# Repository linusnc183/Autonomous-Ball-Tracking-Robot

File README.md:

# Autonomous Ball Tracking Robot

A two-wheeled robot that visually tracks and follows a red ball. A Raspberry Pi handles vision (Picamera2 + OpenCV) and sends drive commands over UART to a custom STM32-based motor controller PCB, which closes the loop with encoder feedback and PID.

I designed the controller PCB from scratch in KiCad and wrote the embedded firmware in C (STM32CubeIDE, HAL).

**Skills demonstrated:** PCB design (KiCad) · embedded C / STM32 HAL · real-time control loops (PID) · analog/digital circuit design (power regulation, signal protection) · computer vision (OpenCV) · serial communication protocol design

https://github.com/user-attachments/assets/ed4e9871-f768-4ec5-b8f6-aebbd3194bc8

## Table of Contents

- [Features](#features)
- [System Architecture](#system-architecture)
- [Hardware](#hardware)
  - [Power](#power-powerkicad_sch)
  - [Motor Driver](#motor-driver-motordriverkicad_sch)
  - [Sensors](#sensors-sensorskicad_sch)
  - [MCU](#mcu-stm32kicad_sch)
  - [Raspberry Pi Interface](#raspberry-pi-interface-raspberrypikicad_sch)
  - [Debug](#debug-debugkicad_sch)
- [Firmware](#firmware-stm32-c--hal-stm32cubeide)
- [Vision](#vision-raspberry-pi-python)
- [Repository Structure](#repository-structure)
- [Getting Started](#getting-started)
- [Testing](#testing)
- [Future Improvements](#future-improvements)

## Features

- Real-time red-ball tracking with Picamera2 + OpenCV
- Custom 2-layer STM32G431 motor controller PCB with protection circuitry
- Closed-loop wheel velocity control via quadrature encoders + independent left/right PID
- UART link between Raspberry Pi and STM32, with a motor-safety timeout if the link drops
- Ultrasonic obstacle sensing (HC-SR04)

## System Architecture

**Why split the work this way:** the Raspberry Pi handles the computationally heavy, non-deterministic side — image processing, ball detection, high-level navigation decisions. The STM32 handles the deterministic, real-time side — PWM generation, encoder feedback, PID control, and motor safety. Keeping them separate means a slow camera frame can never disturb the timing of the motor control loop.

## Hardware

Custom 2-layer controller PCB designed from scratch in KiCad 9 (schematic + layout), organized into hierarchical sheets by subsystem.

### Power (`Power.kicad_sch`)

- **Input:** USB-C receptacle, with 5.1 kΩ pull-down resistors on the CC1/CC2 lines so the port correctly advertises itself to a USB-C source as a 5V/default-current sink.
- **Protection:** A resettable polyfuse (2A) guards the input against overcurrent/short circuits, and SMF5V0A TVS diodes clamp transient voltage spikes on the input.
- **Regulation:** An AP2112K-3.3 LDO steps the 5V USB rail down to 3.3V for the STM32 and logic-level signals, with bulk/decoupling caps (10 µF, 100 µF) on both rails.
- **Status indication:** Power-good LEDs on the 5V and 3.3V rails; test points (TP1–TP3) broken out for probing key rails during bring-up/debug.
- Both 5V and 3.3V are distributed to the Raspberry Pi header, so the Pi is powered directly from the board rather than needing its own separate supply.

### Motor Driver (`MotorDriver.kicad_sch`)

- A single **TB6612FNG** dual H-bridge IC drives both DC motors (one chip, two independent channels — no need for two separate driver ICs).
- The STM32 drives `AIN1/AIN2`/`BIN1/BIN2` for direction and `PWMA`/`PWMB` (from TIM1 CH1/CH2) for speed, with `STBY` used to enable/disable the driver in firmware.
- Bulk capacitance (470 µF + 100 µF) sits close to the motor supply input to absorb the current spikes motors draw on startup/direction changes.
- TVS diodes across the motor connector outputs suppress the inductive kickback/flyback transients DC motors generate when switching direction.

### Sensors (`Sensors.kicad_sch`)

- **HC-SR04 ultrasonic:** `TRIG`/`ECHO` connect directly to the STM32 (PA0/PA1). Since the HC-SR04's echo pin outputs a 5V logic level and the STM32 is 3.3V-tolerant, a resistive divider (20 kΩ/10 kΩ) steps the echo signal down to a safe ~3.3V before it reaches the MCU pin.
- **Quadrature encoders:** Separate 4-pin headers for the left and right motor encoders, each feeding an A/B channel pair into the STM32's hardware timer encoder inputs (TIM3 for one wheel, TIM4 for the other).
- Small filtering capacitors (10 nF) on the encoder/sensor lines help reject electrical noise from the nearby motors.

### MCU (`STM32.kicad_sch`)

- STM32G431CBTx (Arm Cortex-M4, 170 MHz), with standard decoupling capacitors on all supply pins plus a bulk 4.7 µF cap.
- BOOT0 and NRST have pull resistors for reliable reset/boot behavior; two push buttons (SW1/SW2) are broken out for reset and boot-mode selection during flashing/debug.

### Raspberry Pi Interface (`RaspberryPi.kicad_sch`)

- A 4-pin header carries 5V, 3.3V, and UART TX/RX between the board and the Raspberry Pi's GPIO header.
- Series resistors (220 Ω) on the UART lines add a layer of protection against miswiring/contention; no level shifting is needed since both the STM32 and Pi run 3.3V logic.

### Debug (`Debug.kicad_sch`)

- 6-pin SWD header (SWDIO, SWCLK, NRST, 3V3, GND) for programming and debugging the STM32 with an ST-Link, independent of the USART2 link to the Pi.

**Key parts:** STM32G431CBTx · TB6612FNG motor driver · HC-SR04 ultrasonic sensor · 2x quadrature encoders · AP2112K-3.3 LDO · USB-C power input · SMF5V0A TVS protection

## Firmware (STM32, C / HAL, STM32CubeIDE)

| Module | Responsibility |
|---|---|
| `main.c` | System init, 50 Hz control loop scheduling, 10 Hz ultrasonic scheduling |
| `motor.c/h` | PWM + direction output to the TB6612FNG (TIM1 CH1/CH2, AIN/BIN GPIO) |
| `encoder.c/h` | Reads TIM3/TIM4 in quadrature (TI12) encoder mode, converts counts to counts/sec |
| `pid.c/h` | Per-wheel velocity PID with conditional-integration anti-windup |
| `uart_control.c/h` | Parses single-character drive commands from the Pi over USART2 (interrupt-driven) |
| `ultrasonic.c/h` | Software-timed HC-SR04 ranging using the DWT cycle counter for microsecond resolution |

### Control loop

- Runs at 50 Hz (`CONTROL_LOOP_PERIOD_MS = 20`): reads both encoders, runs independent PID controllers for the left/right wheel, and writes the resulting PWM + direction to the motor driver.
- Ultrasonic sensing runs on its own 10 Hz cadence, separate from the control loop, since an HC-SR04 read is a blocking, up-to-30 ms operation and would otherwise disturb the PID's timing.

### PID with anti-windup

Each wheel has an independent PID controller operating on measured wheel speed (encoder counts/sec) with output clamped to a ±1000 PWM range. Integral accumulation uses **conditional integration**: once the output saturates, the integral term stops accumulating unless the error is already pulling it back out of saturation. This prevents the classic windup overshoot where a saturated integrator keeps growing while the motor is already maxed out.

### Quadrature encoding

Wheel encoders are read using the STM32's hardware timer encoder mode (`TIM_ENCODERMODE_TI12`) on TIM3/TIM4, decoding both edges of both channels for full 4x quadrature resolution and reliable direction sensing, rather than software-polling the encoder pins.

### UART command protocol + failsafe

The Pi sends single-byte commands over USART2 (interrupt-driven RX):

| Command | Action |
|---|---|
| `F` | Forward |
| `B` | Backward |
| `L` | Turn left |
| `R` | Turn right |
| `S` | Stop |

If no byte arrives for 500 ms (e.g. the Pi crashes or the link drops), the firmware automatically zeroes both wheel targets and stops the robot — the robot doesn't require a "stop" command to fail safe.

### Ultrasonic ranging without a timer channel

The HC-SR04's echo line isn't wired to a timer input-capture pin, so pulse width is timed in software using the Cortex-M4's DWT cycle counter, giving microsecond-level resolution independent of the main loop's timing.

## Vision (Raspberry Pi, Python)

`ball_tracking.py` captures frames with Picamera2, finds the ball with OpenCV, and streams drive commands to the STM32 over the same UART protocol the firmware implements.

**Detection:** Frames are converted to HSV and thresholded for red across two hue ranges (red wraps around hue 0/180 in OpenCV's HSV space), combined into one mask, then cleaned up with erosion/dilation to remove noise. The largest contour's minimum enclosing circle gives the ball's center and apparent radius.

**Decision logic:** The ball's horizontal offset from frame-center picks a turn command first (turning takes priority so the robot centers on the ball before closing distance); once centered, the ball's apparent radius acts as a distance proxy — small radius drives forward, large radius backs up, and an in-between radius holds position.

**Serial keepalive thread:** The STM32 firmware stops the motors if it doesn't receive a UART byte within 500 ms. Rather than tying that timing to the camera's frame rate, `SerialCommander` runs a dedicated background thread that resends the current command every 150 ms on its own schedule — so a slow or dropped camera frame can never cause an unexpected stop or leave a stale command running longer than intended.

**Debounced ball loss:** Losing the ball for a single frame doesn't stop the robot; it keeps issuing the last command until the ball has been missing for a full second, avoiding jerky stops from momentary detection blips.

Run it with:
```bash
pip install picamera2 opencv-python pyserial numpy
python3 ball_tracking.py
```
Requires UART enabled via `raspi-config` (Interface Options → Serial Port) and, on Pi models where UART is routed through Bluetooth, `dtoverlay=disable-bt` in `/boot/firmware/config.txt`. Wiring: Pi GPIO14 (TX) → STM32 PA3 (RX), Pi GPIO15 (RX) → STM32 PA2 (TX), common ground — both sides are 3.3V logic, no level shifter needed.

## Repository Structure

```
Ball_Tracking_Robot/
├── README.md
├── .gitignore
│
├── hardware/                          # Custom PCB design files
│   └── PCB/
│       ├── KiCad/
│       │   ├── Ball_Tracking_Robot_Controller.kicad_pro
│       │   ├── Ball_Tracking_Robot_Controller.kicad_sch
│       │   ├── Ball_Tracking_Robot_Controller.kicad_pcb
│       │   ├── STM32.kicad_sch
│       │   ├── Power.kicad_sch
│       │   ├── MotorDriver.kicad_sch
│       │   ├── Sensors.kicad_sch
│       │   ├── RaspberryPi.kicad_sch
│       │   └── Debug.kicad_sch
│       ├── Gerbers/                   # Manufacturing files
│       └── BOM/
│
├── firmware/                          # STM32 embedded firmware (STM32CubeIDE project)
│   └── STM32CubeIDE/
│       ├── Core/
│       │   ├── Inc/                   # main.h, motor.h, encoder.h, pid.h,
│       │   │                          # uart_control.h, ultrasonic.h, ...
│       │   └── Src/                   # main.c, motor.c, encoder.c, pid.c,
│       │                              # uart_control.c, ultrasonic.c, ...
│       ├── Drivers/                   # CMSIS + STM32G4xx HAL
│       └── STM32CubeMX/
│           └── Ball_Tracking_Robot.ioc
│
├── software/                          # Raspberry Pi vision code
│   └── RaspberryPi/
│       └── ball_tracking.py
│
├── tests/                             # Hardware/firmware/vision validation
│   ├── uart_test/
│   ├── encoder_test/
│   └── motor_test/
│
└── docs/
    └── images/                        # Schematic screenshots, PCB renders
```

## Getting Started

### Hardware
1. Open `hardware/PCB/KiCad/Ball_Tracking_Robot_Controller.kicad_pro` in [KiCad 9](https://www.kicad.org/).
2. Review the schematics/PCB layout, then generate Gerbers/BOM for fabrication and assembly.

### Firmware
1. Open `firmware/STM32CubeIDE` directly as a project in STM32CubeIDE (targets the STM32G431CBTx).
2. Flash over the onboard SWD header with an ST-Link.
3. Connect USART2 (PA2/PA3) to the Raspberry Pi's UART pins.

### Vision
1. On the Raspberry Pi, install dependencies and run `software/RaspberryPi/ball_tracking.py` (see the [Vision](#vision-raspberry-pi-python) section above for setup details).

## Testing

Validation performed during hardware/firmware bring-up:

- **Hardware:** 3.3V/5V rail verification, UART loopback test, motor driver output check, encoder direction/count check, ultrasonic ranging accuracy check
- **Firmware:** PID step-response tuning, encoder speed measurement validation, UART-disconnect failsafe test (confirms motors stop within 500 ms of link loss)
- **Vision:** red-ball detection under varying lighting conditions, ball-loss/recovery behavior, end-to-end command latency

## Future Improvements

- Replace single-character UART commands with a packet-based protocol (with CRC error checking)
- Add an IMU for orientation estimation
- Add wheel odometry and localization
- Move from manual PID tuning toward autonomous/self-tuning gains
- Full autonomous navigation (beyond ball-following)

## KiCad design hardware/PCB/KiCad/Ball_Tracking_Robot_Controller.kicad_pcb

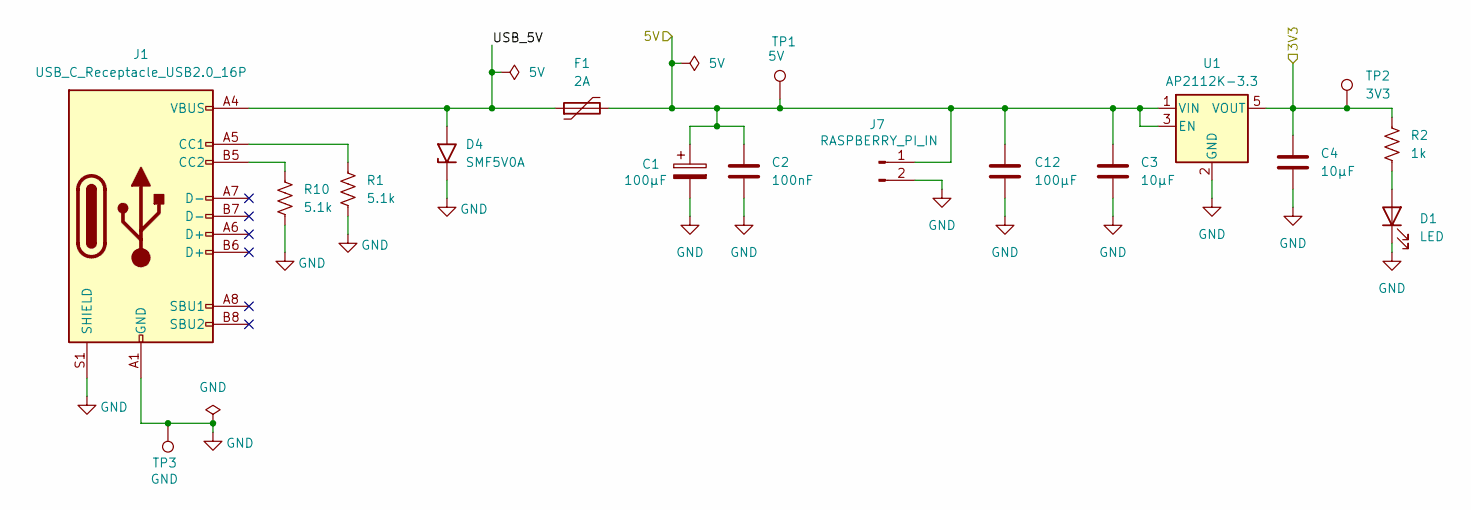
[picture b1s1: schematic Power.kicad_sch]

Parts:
C1: 100μF; C_1206_3216Metric
C2: 100nF; C_0805_2012Metric
C3, C4: 10μF; C_0805_2012Metric
C12: 100μF; C_1210_3225Metric
D1: LED; LED_0805_2012Metric
D4: SMF5V0A; D_SMF
F1: 2A; Fuse_1206_3216Metric
J1: USB_C_Receptacle_USB2.0_16P; USB_C_Receptacle_GCT_USB4105-xx-A_16P_TopMnt_Horizontal
J7: RASPBERRY_PI_IN; PinHeader_1x02_P2.54mm_Vertical
R1, R10: 5.1k; R_0805_2012Metric
R2: 1k; R_0805_2012Metric
TP1: 5V; TestPoint_Pad_D2.0mm
TP2: 3V3; TestPoint_Pad_D2.0mm
TP3: GND; TestPoint_Pad_D2.0mm
U1: AP2112K-3.3; SOT-23-5

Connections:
/Debug/3V3: C4.1, R2.1, TP2.1, U1.5 (VOUT); also elsewhere on the board
/Motor Driver/5V: C1.1, C2.1, C3.1, C12.1, F1.2, J7.1, TP1.1, U1.1 (VIN), U1.3 (EN); also elsewhere on the board
/Power/USB_5V: D4.2 (A2), F1.1, J1.A4 (VBUS), J1.A9 (VBUS), J1.B4 (VBUS), J1.B9 (VBUS)
GND: C1.2, C2.2, C3.2, C4.2, C12.2, D1.1 (K), D4.1 (A1), J1.A1 (GND), J1.A12 (GND), J1.B1 (GND), J1.B12 (GND), J1.S1 (SHIELD), J7.2, R1.2, R10.2, TP3.1, U1.2 (GND); also elsewhere on the board
unnamed: D1.2 (A), R2.2
unnamed: J1.A5 (CC1), R1.1
unnamed: J1.B5 (CC2), R10.1

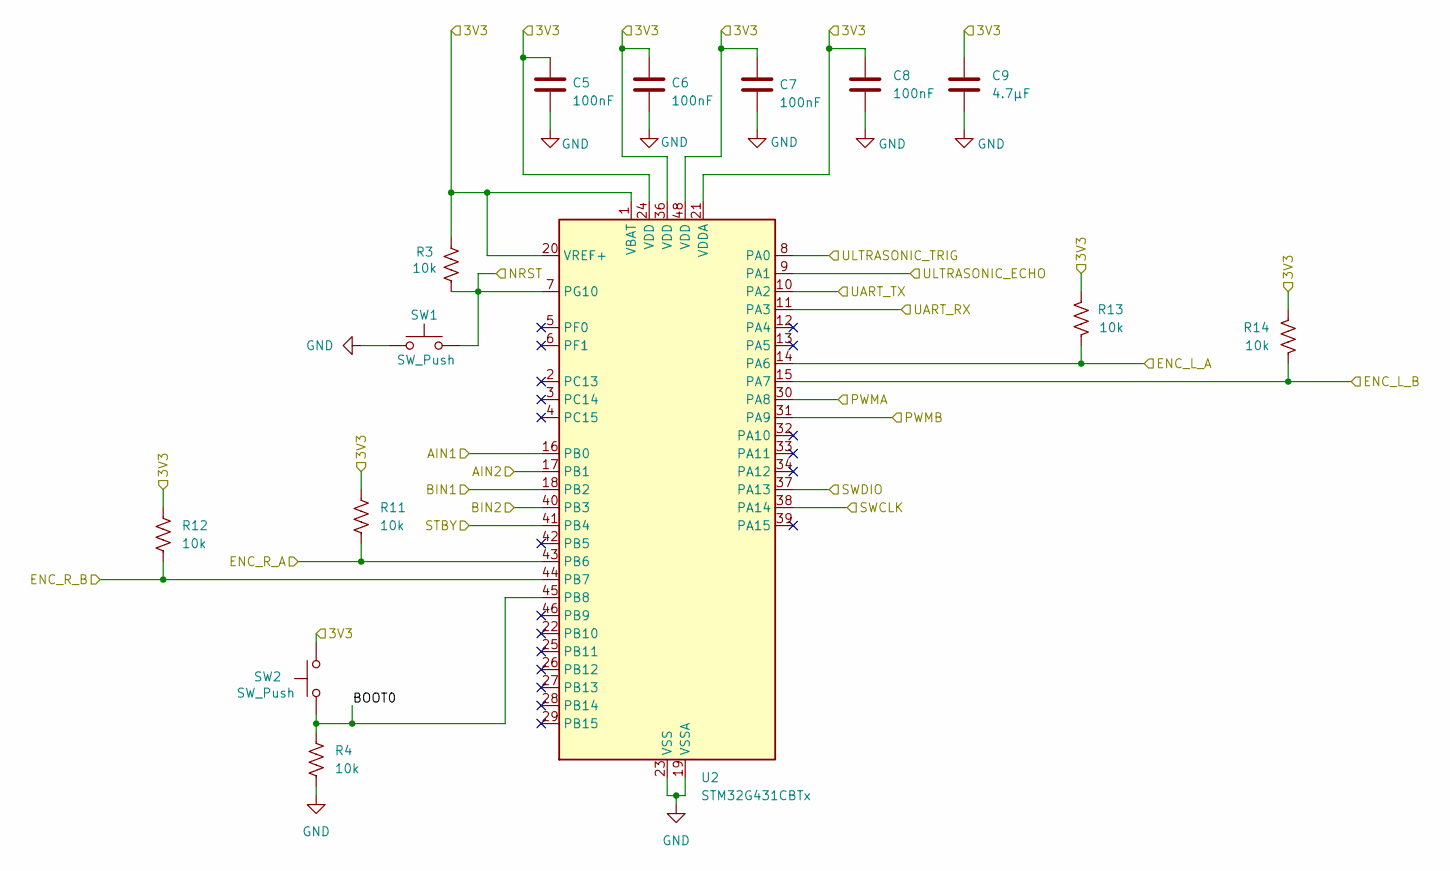
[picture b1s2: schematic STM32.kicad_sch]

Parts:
C5, C6, C7, C8: 100nF; C_0805_2012Metric
C9: 4.7μF; C_0805_2012Metric
R3, R4, R11, R12, R13, R14: 10k; R_0805_2012Metric
SW1, SW2: SW_Push; SW_SPST_TL3305A
U2: STM32G431CBTx; QFN-48-1EP_6x6mm_P0.4mm_EP4.6x4.6mm

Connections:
/Debug/3V3: C5.1, C6.1, C7.1, C8.1, C9.1, R3.1, R11.1, R12.1, R13.1, R14.1, SW2.2, U2.1 (VBAT), U2.20 (VREF+), U2.21 (VDDA), U2.24 (VDD), U2.36 (VDD), U2.48 (VDD); also elsewhere on the board
/Debug/NRST: R3.2, SW1.2, U2.7 (PG10); also elsewhere on the board
/Debug/SWCLK: U2.38 (PA14); also elsewhere on the board
/Debug/SWDIO: U2.37 (PA13); also elsewhere on the board
/Motor Driver/AIN1: U2.16 (PB0); also elsewhere on the board
/Motor Driver/AIN2: U2.17 (PB1); also elsewhere on the board
/Motor Driver/BIN1: U2.18 (PB2); also elsewhere on the board
/Motor Driver/BIN2: U2.40 (PB3); also elsewhere on the board
/Motor Driver/PWMA: U2.30 (PA8); also elsewhere on the board
/Motor Driver/PWMB: U2.31 (PA9); also elsewhere on the board
/Motor Driver/STBY: U2.41 (PB4); also elsewhere on the board
/Raspberry Pi/UART_RX: U2.11 (PA3); also elsewhere on the board
/Raspberry Pi/UART_TX: U2.10 (PA2); also elsewhere on the board
/STM32/BOOT0: R4.1, SW2.1, U2.45 (PB8)
/STM32/ENC_L_A: R13.2, U2.14 (PA6); also elsewhere on the board
/STM32/ENC_L_B: R14.2, U2.15 (PA7); also elsewhere on the board
/STM32/ENC_R_A: R11.2, U2.43 (PB6); also elsewhere on the board
/STM32/ENC_R_B: R12.2, U2.44 (PB7); also elsewhere on the board
/STM32/ULTRASONIC_ECHO: U2.9 (PA1); also elsewhere on the board
/STM32/ULTRASONIC_TRIG: U2.8 (PA0); also elsewhere on the board
GND: C5.2, C6.2, C7.2, C8.2, C9.2, R4.2, SW1.1, U2.19 (VSSA), U2.23 (VSS), U2.35 (VSS), U2.47 (VSS); also elsewhere on the board

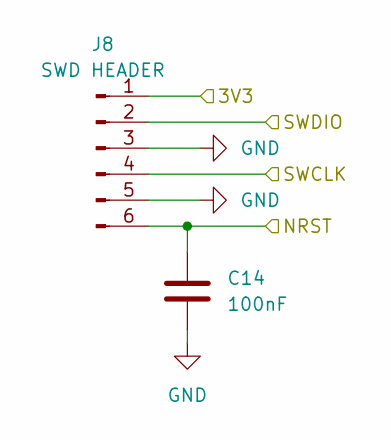
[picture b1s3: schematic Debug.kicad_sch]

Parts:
C14: 100nF; C_0805_2012Metric
J8: SWD HEADER; PinHeader_1x06_P2.54mm_Vertical

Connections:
/Debug/3V3: J8.1; also elsewhere on the board
/Debug/NRST: C14.1, J8.6; also elsewhere on the board
/Debug/SWCLK: J8.4; also elsewhere on the board
/Debug/SWDIO: J8.2; also elsewhere on the board
GND: C14.2, J8.3, J8.5; also elsewhere on the board

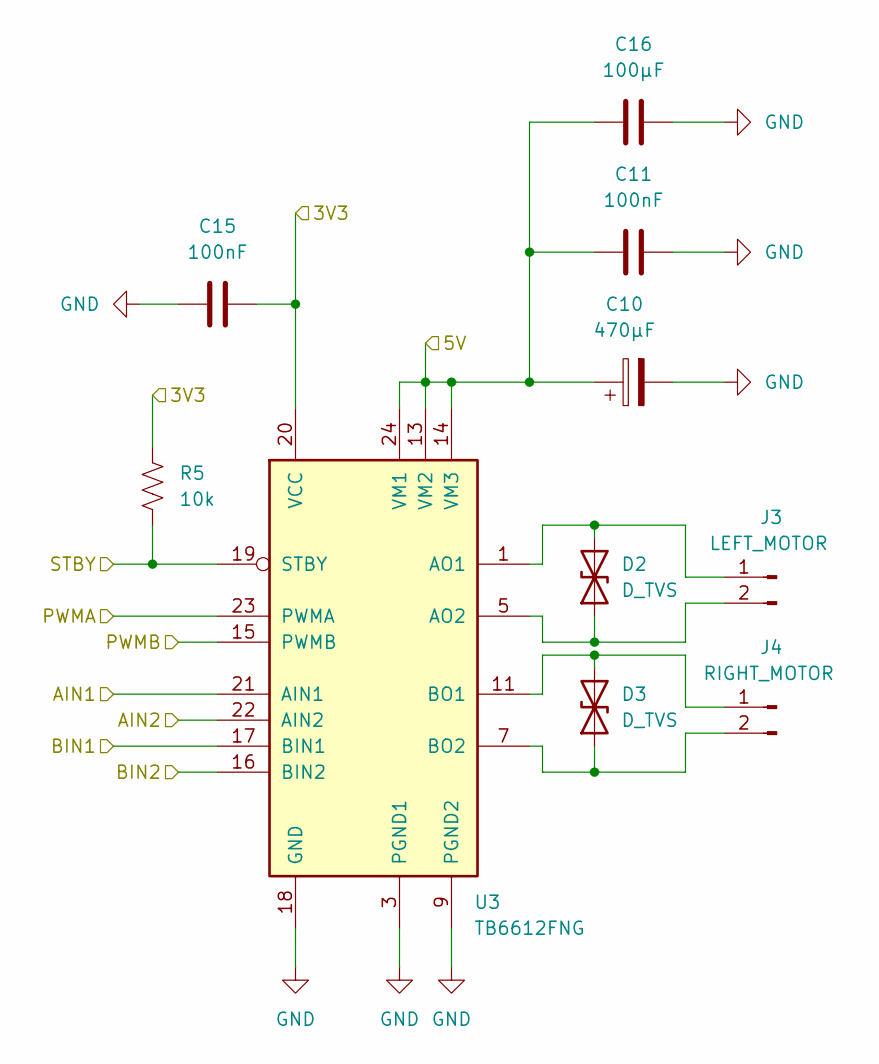
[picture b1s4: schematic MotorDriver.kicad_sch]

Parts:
C10: 470μF; C_Elec_6.3x5.8
C11, C15: 100nF; C_0805_2012Metric
C16: 100μF; C_1206_3216Metric
D2, D3: D_TVS; D_SMA
J3: LEFT_MOTOR; JST_VH_B2P-VH_1x02_P3.96mm_Vertical
J4: RIGHT_MOTOR; JST_VH_B2P-VH_1x02_P3.96mm_Vertical
R5: 10k; R_0805_2012Metric
U3: TB6612FNG; HTSSOP-24-1EP_4.4x7.8mm_P0.65mm_EP3.4x7.8mm_Mask2.4x4.68mm

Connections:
/Debug/3V3: C15.2, R5.1, U3.20 (VCC); also elsewhere on the board
/Motor Driver/5V: C10.1, C11.1, C16.1, U3.13 (VM2), U3.14 (VM3), U3.24 (VM1); also elsewhere on the board
/Motor Driver/AIN1: U3.21 (AIN1); also elsewhere on the board
/Motor Driver/AIN2: U3.22 (AIN2); also elsewhere on the board
/Motor Driver/BIN1: U3.17 (BIN1); also elsewhere on the board
/Motor Driver/BIN2: U3.16 (BIN2); also elsewhere on the board
/Motor Driver/PWMA: U3.23 (PWMA); also elsewhere on the board
/Motor Driver/PWMB: U3.15 (PWMB); also elsewhere on the board
/Motor Driver/STBY: R5.2, U3.19 (STBY); also elsewhere on the board
GND: C10.2, C11.2, C15.1, C16.2, U3.3 (PGND1), U3.4 (PGND1), U3.9 (PGND2), U3.10 (PGND2), U3.18 (GND); also elsewhere on the board
unnamed: D2.1 (A1), J3.2, U3.5 (AO2), U3.6 (AO2)
unnamed: D2.2 (A2), J3.1, U3.1 (AO1), U3.2 (AO1)
unnamed: D3.1 (A1), J4.2, U3.7 (BO2), U3.8 (BO2)
unnamed: D3.2 (A2), J4.1, U3.11 (BO1), U3.12 (BO1)

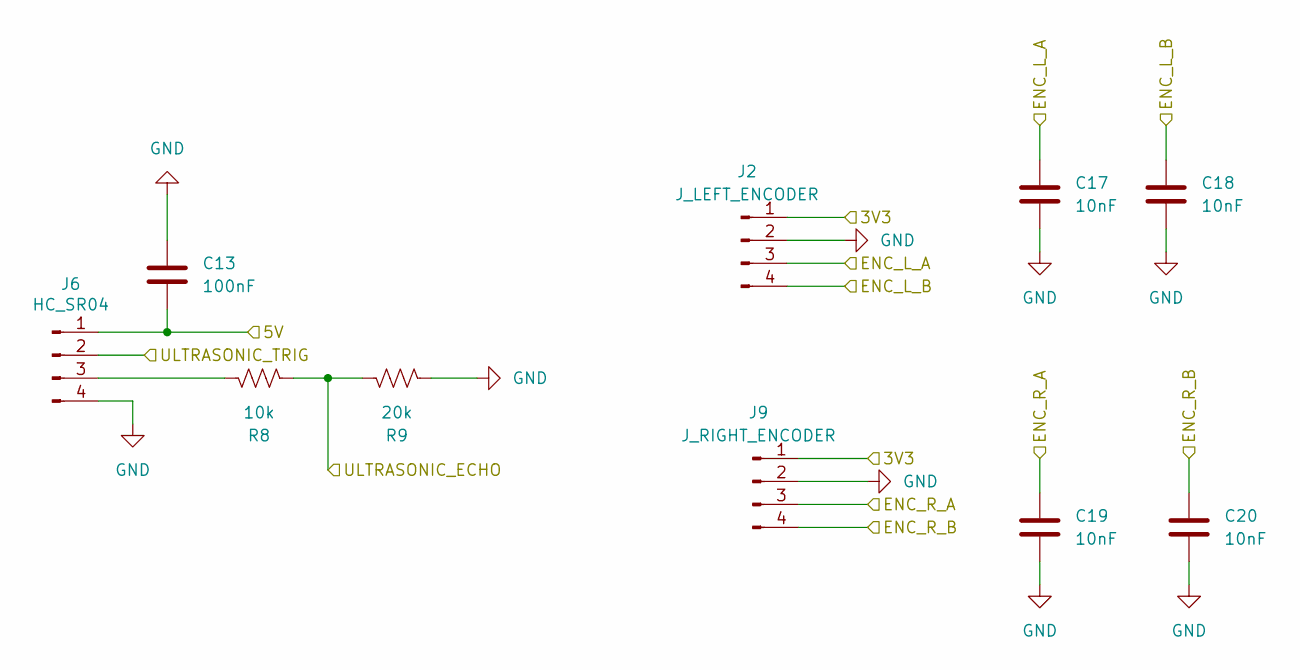
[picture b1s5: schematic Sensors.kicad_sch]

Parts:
C13: 100nF; C_0805_2012Metric
C17, C18, C19, C20: 10nF; C_0805_2012Metric
J2: J_LEFT_ENCODER; PinHeader_1x04_P2.54mm_Vertical
J6: HC_SR04; PinHeader_1x04_P2.54mm_Vertical
J9: J_RIGHT_ENCODER; PinHeader_1x04_P2.54mm_Vertical
R8: 10k; R_0805_2012Metric
R9: 20k; R_0805_2012Metric

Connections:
/Debug/3V3: J2.1, J9.1; also elsewhere on the board
/Motor Driver/5V: C13.2, J6.1; also elsewhere on the board
/STM32/ENC_L_A: C17.1, J2.3; also elsewhere on the board
/STM32/ENC_L_B: C18.1, J2.4; also elsewhere on the board
/STM32/ENC_R_A: C19.1, J9.3; also elsewhere on the board
/STM32/ENC_R_B: C20.1, J9.4; also elsewhere on the board
/STM32/ULTRASONIC_ECHO: R8.2, R9.1; also elsewhere on the board
/STM32/ULTRASONIC_TRIG: J6.2; also elsewhere on the board
GND: C13.1, C17.2, C18.2, C19.2, C20.2, J2.2, J6.4, J9.2, R9.2; also elsewhere on the board
unnamed: J6.3, R8.1

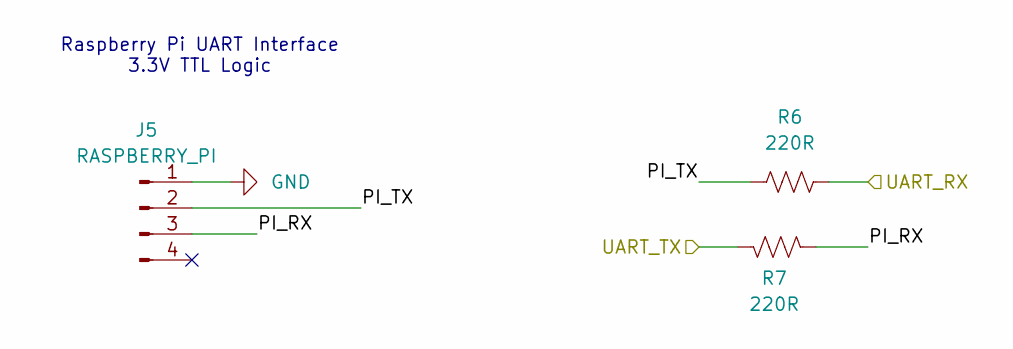
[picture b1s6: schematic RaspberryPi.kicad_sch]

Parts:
J5: RASPBERRY_PI; PinHeader_1x04_P2.54mm_Vertical
R6, R7: 220R; R_0805_2012Metric

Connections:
/Raspberry Pi/PI_RX: J5.3, R7.2
/Raspberry Pi/PI_TX: J5.2, R6.1
/Raspberry Pi/UART_RX: R6.2; also elsewhere on the board
/Raspberry Pi/UART_TX: R7.1; also elsewhere on the board
GND: J5.1; also elsewhere on the board

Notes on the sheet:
Raspberry Pi UART Interface 3.3V TTL Logic

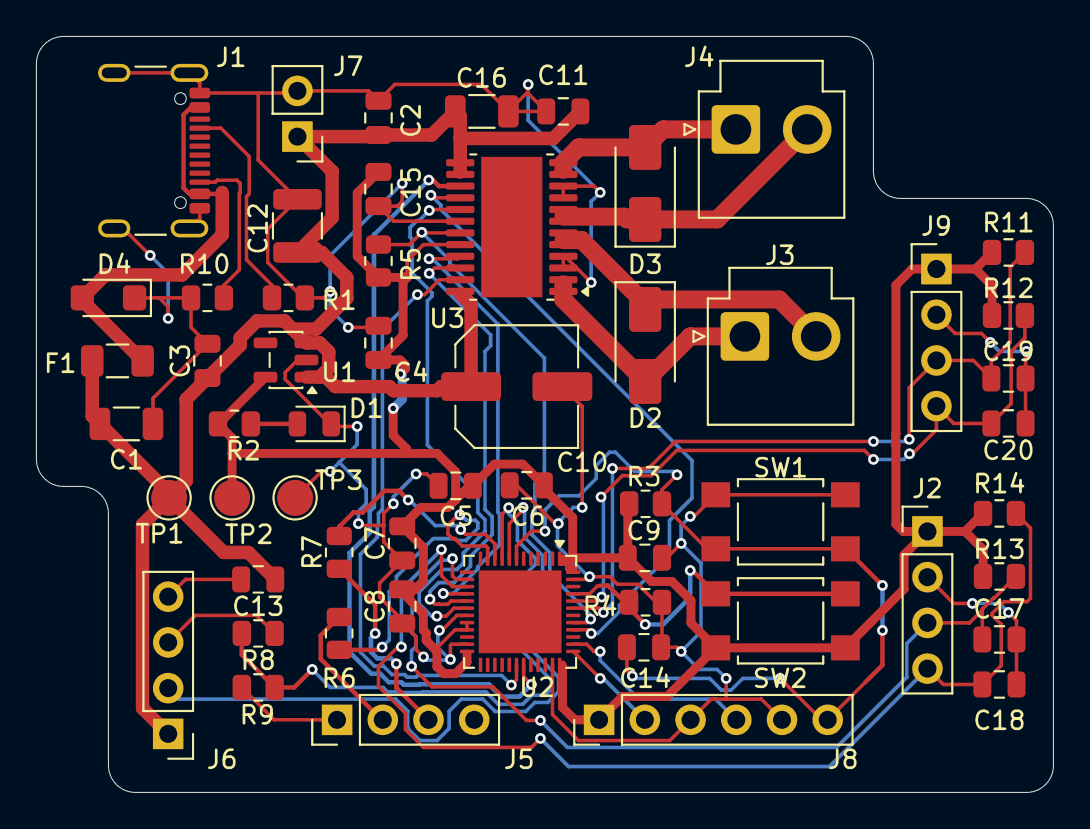
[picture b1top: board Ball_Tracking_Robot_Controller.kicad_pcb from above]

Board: 2 copper layers, 56.5 x 42.0 mm, 56 parts (0 on the bottom side), 33 nets.

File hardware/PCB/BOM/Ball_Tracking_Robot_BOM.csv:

"Reference","Qty","Value","DNP","Exclude from BOM","Exclude from Board","Footprint","Datasheet"
"C1,C16","2","100μF","","","","Capacitor_SMD:C_1206_3216Metric","~"
"C2,C5,C6,C7,C8,C11,C13,C14,C15","9","100nF","","","","Capacitor_SMD:C_0805_2012Metric","~"
"C3,C4","2","10μF","","","","Capacitor_SMD:C_0805_2012Metric","~"
"C9","1","4.7μF","","","","Capacitor_SMD:C_0805_2012Metric","~"
"C10","1","470μF","","","","Capacitor_SMD:C_Elec_6.3x5.8","~"
"C12","1","100μF","","","","Capacitor_SMD:C_1210_3225Metric","~"
"C17,C18,C19,C20","4","10nF","","","","Capacitor_SMD:C_0805_2012Metric","~"
"D1","1","LED","","","","LED_SMD:LED_0805_2012Metric","~"
"D2,D3","2","D_TVS","","","","Diode_SMD:D_SMA","~"
"D4","1","SMF5V0A","","","","Diode_SMD:D_SMF","https://www.vishay.com/doc?85881"
"F1","1","2A","","","","Fuse:Fuse_1206_3216Metric","~"
"J1","1","USB_C_Receptacle_USB2.0_16P","","","","Connector_USB:USB_C_Receptacle_GCT_USB4105-xx-A_16P_TopMnt_Horizontal","https://www.usb.org/sites/default/files/documents/usb_type-c.zip"
"J2","1","J_LEFT_ENCODER","","","","Connector_PinHeader_2.54mm:PinHeader_1x04_P2.54mm_Vertical","~"
"J3","1","LEFT_MOTOR","","","","Connector_JST:JST_VH_B2P-VH_1x02_P3.96mm_Vertical","~"
"J4","1","RIGHT_MOTOR","","","","Connector_JST:JST_VH_B2P-VH_1x02_P3.96mm_Vertical","~"
"J5","1","RASPBERRY_PI","","","","Connector_PinHeader_2.54mm:PinHeader_1x04_P2.54mm_Vertical","~"
"J6","1","HC_SR04","","","","Connector_PinHeader_2.54mm:PinHeader_1x04_P2.54mm_Vertical","~"
"J7","1","RASPBERRY_PI_IN","","","","Connector_PinHeader_2.54mm:PinHeader_1x02_P2.54mm_Vertical","~"
"J8","1","SWD HEADER","","","","Connector_PinHeader_2.54mm:PinHeader_1x06_P2.54mm_Vertical","~"
"J9","1","J_RIGHT_ENCODER","","","","Connector_PinHeader_2.54mm:PinHeader_1x04_P2.54mm_Vertical","~"
"R1,R10","2","5.1k","","","","Resistor_SMD:R_0805_2012Metric","~"
"R2","1","1k","","","","Resistor_SMD:R_0805_2012Metric","~"
"R3,R4,R5,R8,R11,R12,R13,R14","8","10k","","","","Resistor_SMD:R_0805_2012Metric","~"
"R6,R7","2","220R","","","","Resistor_SMD:R_0805_2012Metric","~"
"R9","1","20k","","","","Resistor_SMD:R_0805_2012Metric","~"
"SW1,SW2","2","SW_Push","","","","Button_Switch_SMD:SW_SPST_TL3305A","~"
"TP1","1","5V","","","","TestPoint:TestPoint_Pad_D2.0mm","~"
"TP2","1","3V3","","","","TestPoint:TestPoint_Pad_D2.0mm","~"
"TP3","1","GND","","","","TestPoint:TestPoint_Pad_D2.0mm","~"
"U1","1","AP2112K-3.3","","","","Package_TO_SOT_SMD:SOT-23-5","https://www.diodes.com/assets/Datasheets/AP2112.pdf"
"U2","1","STM32G431CBTx","","","","Package_DFN_QFN:QFN-48-1EP_6x6mm_P0.4mm_EP4.6x4.6mm","https://www.st.com/resource/en/datasheet/stm32g431cb.pdf"
"U3","1","TB6612FNG","","","","Package_SO:HTSSOP-24-1EP_4.4x7.8mm_P0.65mm_EP3.4x7.8mm_Mask2.4x4.68mm","https://toshiba.semicon-storage.com/us/product/linear/motord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"

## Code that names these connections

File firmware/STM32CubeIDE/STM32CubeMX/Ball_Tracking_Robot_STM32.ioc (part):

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Mcu.Name=STM32G431C(6-8-B)Tx
Mcu.Package=LQFP48
Mcu.UserName=STM32G431CBTx
PA0.GPIOParameters=GPIO_Label
PA0.GPIO_Label=ULTRASONIC_TRIG
PA0.Signal=GPIO_Output
PA1.GPIOParameters=GPIO_Label
PA1.GPIO_Label=ULTRASONIC_ECHO
PA1.Signal=GPIO_Input
PA13.Mode=Serial_Wire
PA13.Signal=SYS_JTMS-SWDIO
PA14.Mode=Serial_Wire
PA14.Signal=SYS_JTCK-SWCLK
PA2.GPIOParameters=GPIO_Label
PA2.GPIO_Label=PI_TX
PA2.Mode=Asynchronous
PA2.Signal=USART2_TX
PA3.GPIOParameters=GPIO_Label
PA3.GPIO_Label=PI_RX
PA3.Mode=Asynchronous
PA3.Signal=USART2_RX
PA6.Signal=S_TIM3_CH1
PA7.Signal=S_TIM3_CH2
PA8.Signal=S_TIM1_CH1
PA9.Signal=S_TIM1_CH2
PB0.GPIOParameters=GPIO_Label
PB0.GPIO_Label=AIN1
PB0.Signal=GPIO_Output
PB1.GPIOParameters=GPIO_Label
PB1.GPIO_Label=AIN2
PB1.Signal=GPIO_Output
PB2.GPIOParameters=GPIO_Label
PB2.GPIO_Label=BIN1
PB2.Signal=GPIO_Output
PB3.GPIOParameters=GPIO_Label
PB3.GPIO_Label=BIN2
PB3.Signal=GPIO_Output
PB4.GPIOParameters=GPIO_Label
PB4.GPIO_Label=STBY
PB4.Signal=GPIO_Output
PB6.Signal=S_TIM4_CH1
PB7.Signal=S_TIM4_CH2
RCC.HSE_VALUE=8000000
RCC.SYSCLKFreq_VALUE=170000000
RCC.SYSCLKSource=RCC_SYSCLKSOURCE_PLLCLK
board=custom
